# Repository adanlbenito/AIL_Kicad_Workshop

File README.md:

##  Kicad 5
* [Download link](https://kicad-pcb.org/download/)

## Libraries

### Kicad
* [Symbols](https://github.com/kicad/kicad-symbols)
* [Footprints](https://github.com/KiCad/kicad-footprints)
* [3D Models](https://github.com/KiCad/kicad-packages3D)

### Digi-Key
* [Github link](https://github.com/Digi-Key/digikey-kicad-library)
* [How to import](https://forum.digikey.com/t/importing-the-digi-key-kicad-library-into-kicad-5-0-0/4075)

### SparkFun
* [Github link](https://github.com/sparkfun/SparkFun-KiCad-Libraries/tree/master/Footprints)

### SnapEDA
* [link](https://www.snapeda.com/home/)

## Action plugins
* [InteractiveHtmlBom](https://github.com/openscopeproject/InteractiveHtmlBom)
* [RF-tools-KiCAD](https://github.com/Digi-Key/digikey-kicad-library)
* [ViaStitching + CircuilarZone](https://github.com/jsreynaud/kicad-action-scripts)
* [Teardrops](https://github.com/NilujePerchut/kicad_scripts)
* [Replicate Layout](https://github.com/MitjaNemec/Kicad_action_plugins)
* [KiKit: panelizatiobn](https://github.com/yaqwsx/KiKit)
* [svg2shenzhen](https://github.com/badgeek/svg2shenzhen)

## Other resources
* [Interesting Engineering youtube channel](https://www.youtube.com/channel/UCkJRycUz2CylxpiP-zMePow)
* [Hackaday U Kicad + Freecad course](https://hackaday.io/project/172360-introduction-to-kicad-and-freecad)
* [Digikey tutorial](https://www.digikey.com/en/resources/design-tools/kicad)
* [More tutorials](https://kicad-pcb.org/help/tutorials/) (keep in mind that Kicad changed quite a lot on the latest revisions so older tutorials may be confusing).

## Kicad Conference: KiCon
* [2020 edition (online)](https://2020.kicad-kicon.com/)

# Resources for reference design

## Power Amp

* [Digi-Key Part](https://www.digikey.ca/en/products/detail/texas-instruments/TPA2016D2RTJR/2183791)
* [Datasheet](https://www.ti.com/general/docs/suppproductinfo.tsp?distId=10&gotoUrl=http%3A%2F%2Fwww.ti.com%2Flit%2Fgpn%2Ftpa2016d2)
* [SnapEDA](https://www.snapeda.com/parts/TPA2016D2RTJR/Texas%20Instruments/view-part/?ref=search&t=TPA2016)

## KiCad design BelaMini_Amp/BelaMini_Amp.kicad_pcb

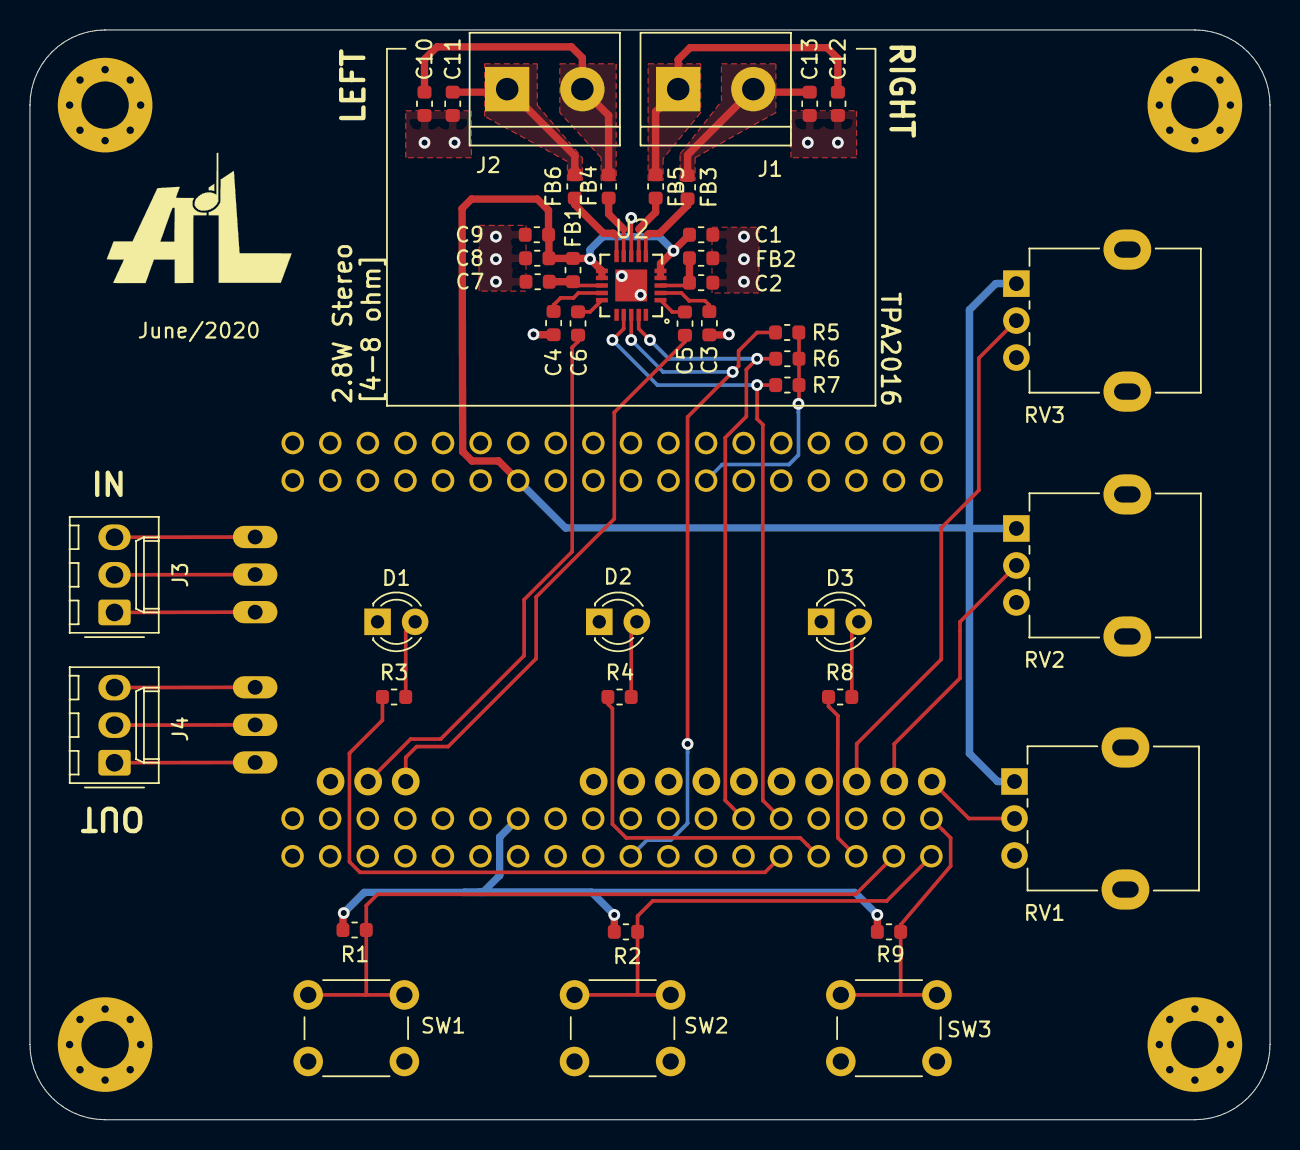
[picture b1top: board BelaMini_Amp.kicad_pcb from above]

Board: 2 copper layers, 83.8 x 73.7 mm, 43 parts (1 on the bottom side), 38 nets.

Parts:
C1, C2, C7: 100nF; C_0603_1608Metric
C3, C4, C5, C6, C9: 1uF; C_0603_1608Metric
C8: 10uF; C_0603_1608Metric
C10, C11, C12, C13: 1nF; C_0603_1608Metric
D1, D2, D3: LED; LED_D3.0mm
FB1, FB2: Ferrite_Bead_Small; L_0603_1608Metric
FB3, FB4, FB5, FB6: MPZ1608S221A; L_0603_1608Metric
J1: OUT_L; TerminalBlock_bornier-2_P5.08mm
J2: OUT_R; TerminalBlock_bornier-2_P5.08mm
J3, J4: Conn_01x03_Female; Molex_KK-254_AE-6410-03A_1x03_P2.54mm_Vertical
R1, R2, R9: 1k; R_0603_1608Metric
R3, R4, R8: 470; R_0603_1608Metric
R5: 100k; R_0603_1608Metric
R6, R7: 10k; R_0603_1608Metric
RV1, RV2, RV3: R_POT; Potentiometer_Alpha_RD901F-40-00D_Single_Vertical
SW1, SW2, SW3: SW_Push; SW_PUSH_6mm
U1: BelaMini; BelaMini_headers_reverse
U2: TPA2016D2RTJR; QFN50P400X400X80-21N

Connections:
3.3V: R1.1, R2.1, R5.1, R6.2, R7.2, R9.1, U1.P1_14, U1.P2_23
5V: C1.1, C8.1, C9.1, FB1.1, RV1.1, RV2.1, RV3.1, U1.P1_24, U2.4, U2.5, U2.11, U2.12
/A0: RV1.2, U1.A0
/A1: RV2.2, U1.A1
/A2: RV3.2, U1.A2
/Audio_In_L: J3.2, U1.Audio_In_L
/Audio_In_R: J3.1, U1.Audio_In_R
/Audio_Out_L: J4.2, U1.Audio_Out_L
/Audio_Out_R: J4.1, U1.Audio_Out_R
/D0: R9.2, SW3.2, U1.P2_01
/D1: R2.2, SW2.2, U1.P2_02
/D2: R1.2, SW1.2, U1.P2_04
/D3: R8.1, U1.P2_06
/D4: R4.1, U1.P2_08
/D5: R3.1, U1.P2_10
/D6: R5.2, U1.P2_18, U2.18
/LINE_L: C6.2, U1.Line_L
/LINE_R: C5.2, U1.Line_R
/SCL: R7.1, U1.P2_09, U2.17
/SDA: R6.1, U1.P2_11, U2.19
GND: C1.2, C2.2, C3.2, C4.2, C7.2, C8.2, C9.2, C10.2, C11.2, C12.2, C13.2, D1.1, D2.1, D3.1, FB2.1, J3.3, J4.3, RV1.3, RV2.3, RV3.3, SW1.1, SW2.1, SW3.1, U1.A_GND, U1.Audio_GND, U1.Line_GND, U1.P1_16, U1.P1_22, U1.P2_21, U2.8, U2.21
GNDA: C2.1, FB2.2, U2.3
unnamed: C3.1, U2.2
unnamed: C4.1, U2.14
unnamed: C5.1, U2.1
unnamed: C6.1, U2.15
unnamed: C10.1, FB4.1, J2.2
unnamed: C11.1, FB6.1, J2.1
unnamed: C12.1, FB5.1, J1.1
unnamed: C13.1, FB3.1, J1.2
unnamed: D1.2, R3.2
unnamed: D2.2, R4.2
unnamed: D3.2, R8.2
unnamed: FB3.2, U2.6
unnamed: FB4.2, U2.9
unnamed: FB5.2, U2.7
unnamed: FB6.2, U2.10
VDDA: C7.1, FB1.2, U2.13

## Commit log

2020-06-19 Add Bela Mini libraries
2020-06-19 Add Stereo Power Amp schematic
2020-06-19 Add finalised design
2020-06-19 Added slides
2020-07-01 Updated example
2020-07-01 Added AIL logo bmp and footprint
2020-07-01 Added amplifier footprint from SnapEDA. Added comments to schematic.
2020-07-01 Added more resources
2020-07-01 Updated slides
2020-07-01 Added design resulting from worskhop
